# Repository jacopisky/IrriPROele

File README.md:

# IrriPROele
A simple irrigation controller system up to 6 AC and 4 DC valves + pump protection

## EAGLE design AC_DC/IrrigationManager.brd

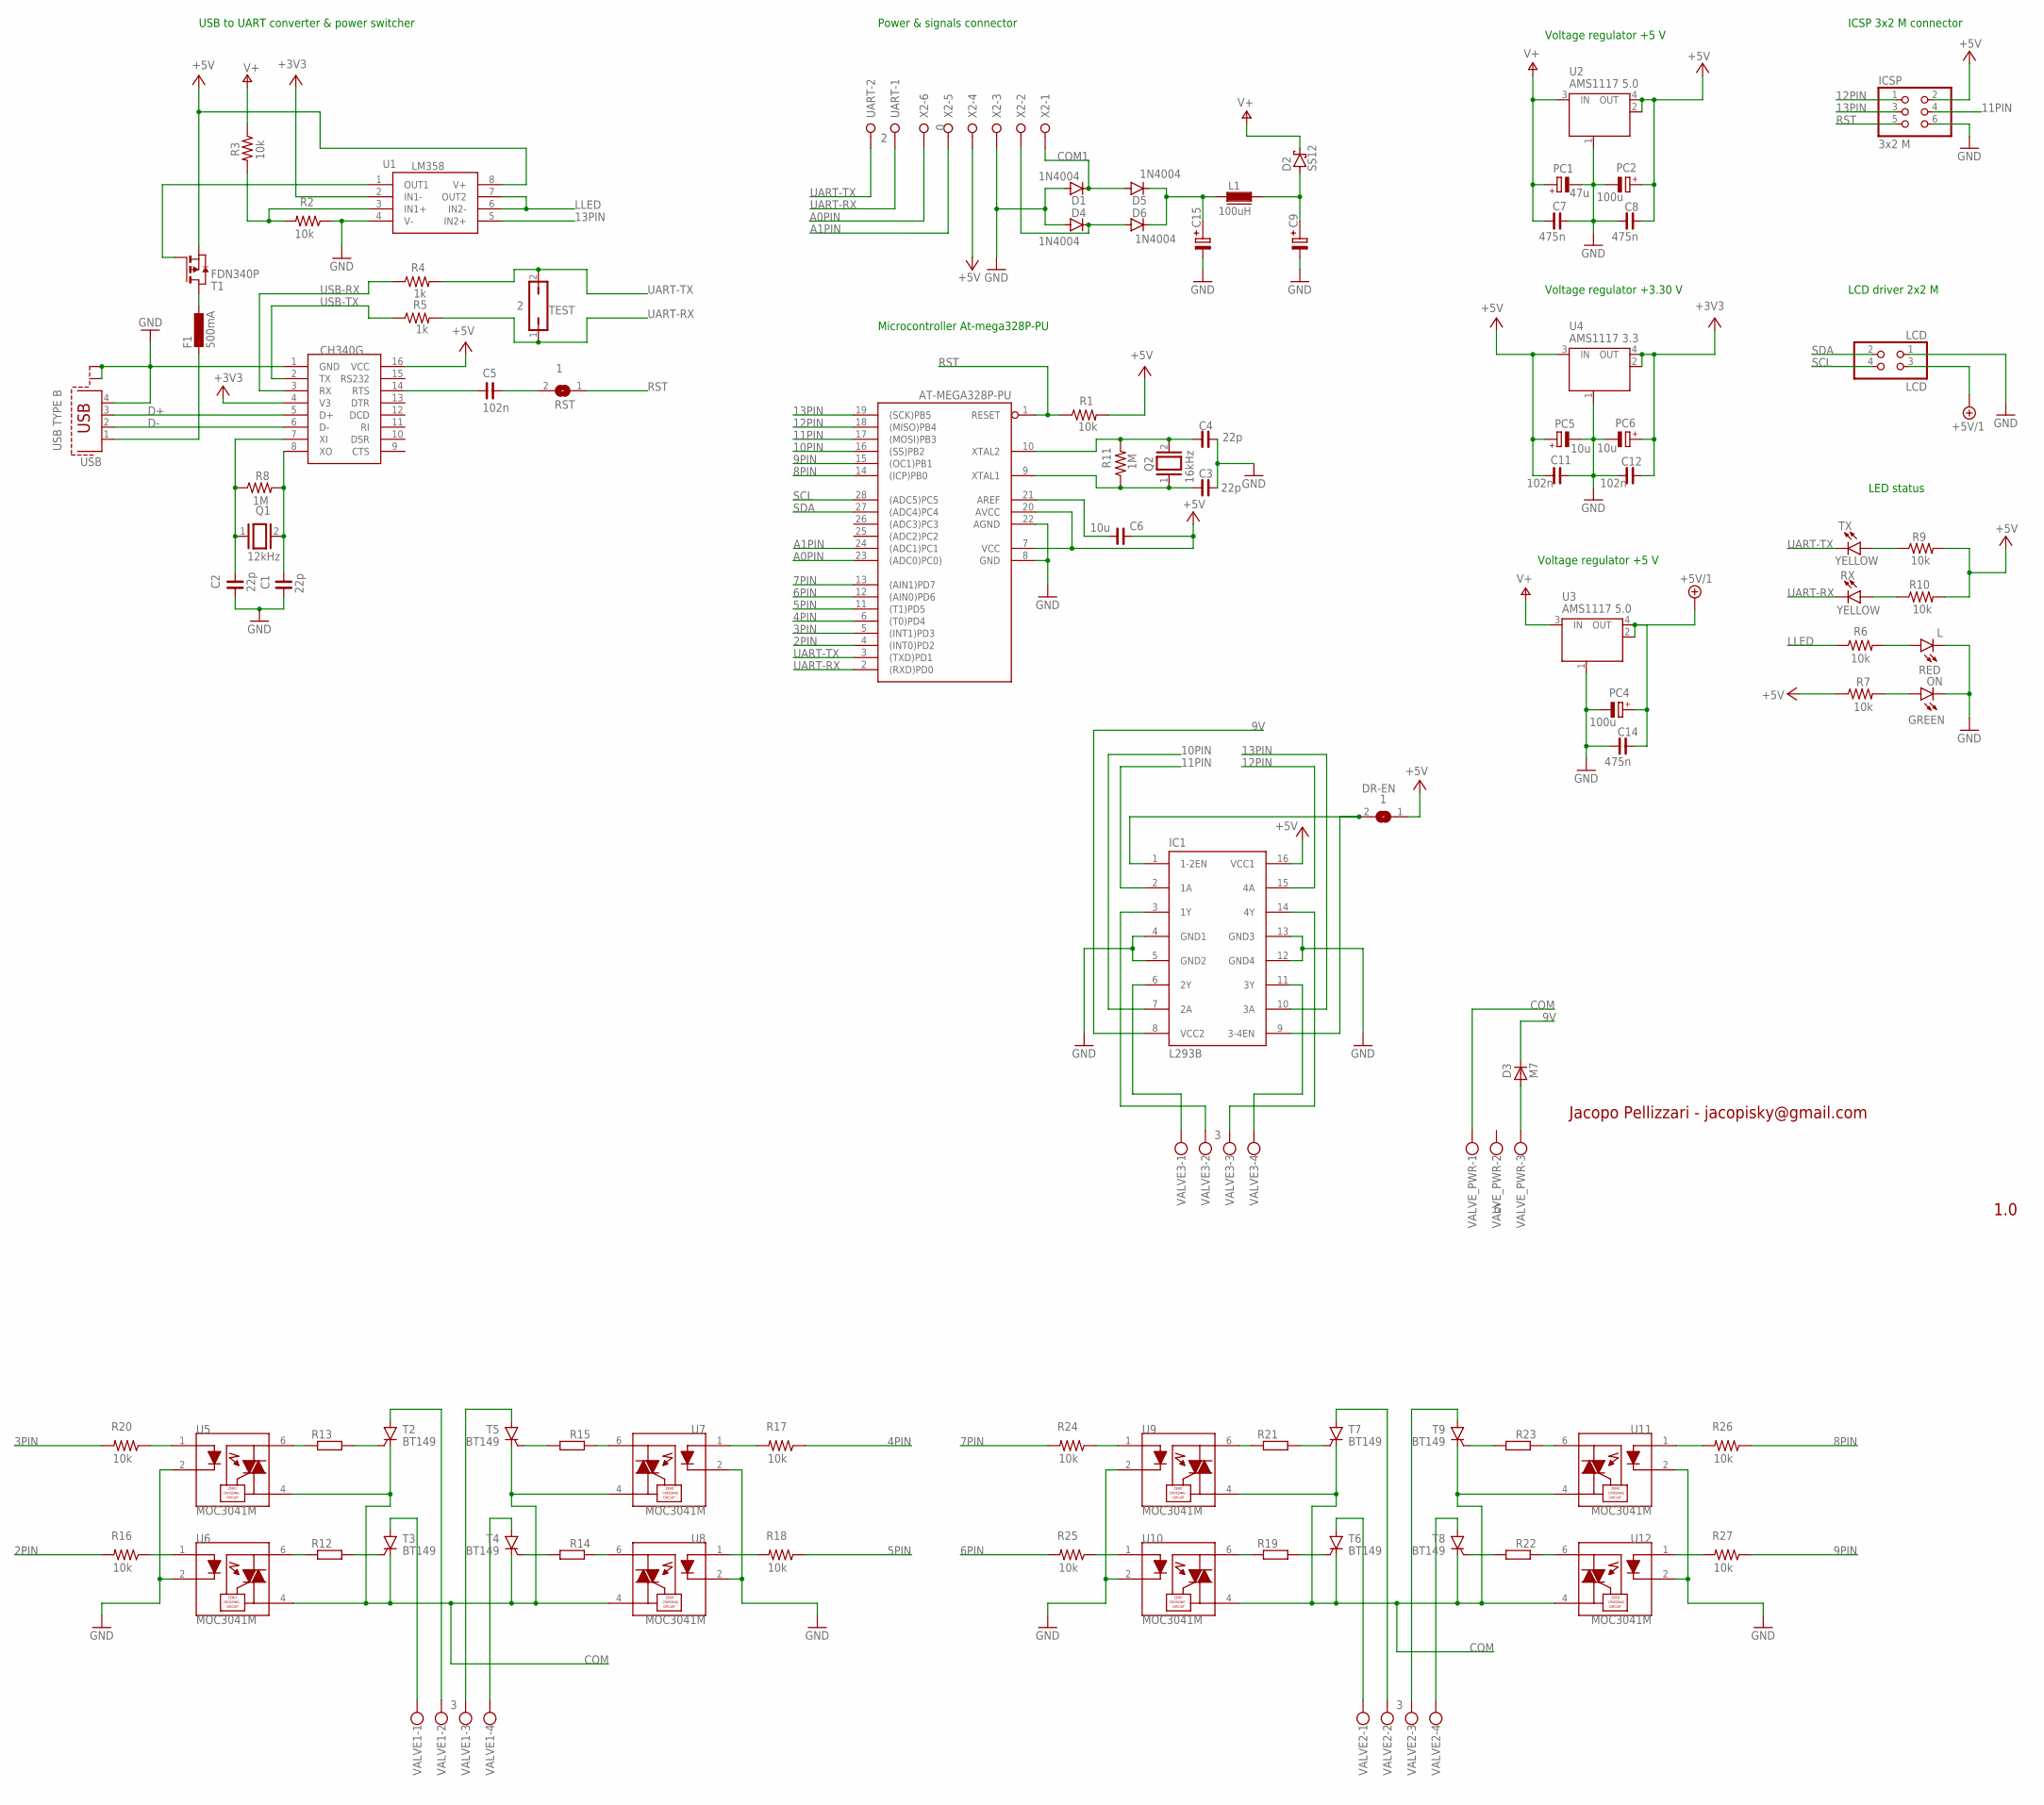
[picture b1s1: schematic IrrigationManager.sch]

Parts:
AT-MEGA328P-PU: ATMEGA328P-PU; DIL28-3
C1, C2, C3, C4: 22p; C1206
C5, C11, C12: 102n; C1206
C6: 10u; C1206
C7, C8, C14: 475n; C1206
C9, C15: C-PR-5,0X10; E5,0-10
D1, D4, D5, D6: 1N4004; DO41-10
D2: SS12; SMA
D3: M7; SMB
DR-EN: 1; SJ
F1: 500mA; L1812
IC1: L293B; DIL16
ICSP: 3x2 M; 2X03
L: RED; CHIPLED_1206
L1: 100uH; FASTRON_07HCP_INDUCTOR
LCD: LCD; 2X02
ON: GREEN; CHIPLED_1206
PC1: 47u; PANASONIC_D
PC2, PC4: 100u; PANASONIC_D
PC5, PC6: 10u; 153CLV-0405
Q1: 12kHz; QS
Q2: 16kHz; QS
R1, R2, R3, R6, R7, R9, R10, R16, R17, R18, R20, R24, R25, R26, R27: 10k; RES_1206
R4, R5: 1k; RES_1206
R8, R11: 1M; RES_1206
R12, R13, R14, R15, R19, R21, R22, R23: R-EU_0204/7; 0204/7
RST: 1; SJ
RX: YELLOW; CHIPLED_1206
T1: FDN340P; SOT-23
T2, T3, T4, T5, T6, T7, T8, T9: BT149; TO92-4
TEST: 2; JP1
TX: YELLOW; CHIPLED_1206
U1: LM358; LM358DR
U2, U3: AMS1117 5.0; SOT223
U4: AMS1117 3.3; SOT223
U5, U6, U7, U8, U9, U10, U11, U12: MOC3041M; DIP762W46P254L889H508Q6
U$1: CH340G; SOIC16
UART: 2; W237-132
USB: USB TYPE B; PN61729-S
VALVE1, VALVE2, VALVE3: 3; W237-4P
VALVE_PWR: 6; W237-133
X2: 0; W237-6P

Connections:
2PIN: AT-MEGA328P-PU.4 ((INT0)PD2), R16.2
3PIN: AT-MEGA328P-PU.5 ((INT1)PD3), R20.2
4PIN: AT-MEGA328P-PU.6 ((T0)PD4), R17.1
5PIN: AT-MEGA328P-PU.11 ((T1)PD5), R18.1
5VP: T1.3 (G), U1.1 (OUT1)
6PIN: AT-MEGA328P-PU.12 ((AIN0)PD6), R25.2
7PIN: AT-MEGA328P-PU.13 ((AIN1)PD7), R24.2
8PIN: AT-MEGA328P-PU.14 ((ICP)PB0), R26.1
9PIN: AT-MEGA328P-PU.15 ((OC1)PB1), R27.1
9V: D3.C, IC1.8 (VCC2)
10PIN: AT-MEGA328P-PU.16 ((SS)PB2), IC1.7 (2A)
11PIN: AT-MEGA328P-PU.17 ((MOSI)PB3), IC1.2 (1A), ICSP.4
12PIN: AT-MEGA328P-PU.18 ((MISO)PB4), IC1.15 (4A), ICSP.1
13PIN: AT-MEGA328P-PU.19 ((SCK)PB5), IC1.10 (3A), ICSP.3, U1.5 (IN2+)
+3V3: C12.2, PC6.+, U1.2 (IN1-), U4.2 (OUT), U4.4 (OUT), U$1.4 (V3)
+5V: AT-MEGA328P-PU.7 (VCC), AT-MEGA328P-PU.20 (AVCC), C6.2, C8.2, C11.1, DR-EN.1, IC1.16 (VCC1), ICSP.2, PC2.+, PC5.+, R1.2, R7.1, R9.2, R10.2, T1.2 (S), U1.8 (V+), U2.2 (OUT), U2.4 (OUT), U4.3 (IN), U$1.16 (VCC), X2.4
+5V/1: C14.2, LCD.3, PC4.+, U3.2 (OUT), U3.4 (OUT)
A0PIN: AT-MEGA328P-PU.23 ((ADC0)PC0)), X2.6
A1PIN: AT-MEGA328P-PU.24 ((ADC1)PC1), X2.5
COM: T2.C, T3.C, T4.C, T5.C, T6.C, T7.C, T8.C, T9.C, U5.4 (MT1), U6.4 (MT1), U7.4 (MT1), U8.4 (MT1), U9.4 (MT1), U10.4 (MT1), U11.4 (MT1), U12.4 (MT1), VALVE_PWR.1
COM1: D1.C, D5.A, X2.1
CRST: C5.1, U$1.14 (RTS)
D+: U$1.5 (D+), USB.3
D-: U$1.6 (D-), USB.2
FUSE5V: F1.1, T1.1 (D)
GND: AT-MEGA328P-PU.8 (GND), AT-MEGA328P-PU.22 (AGND), C1.1, C2.1, C3.2, C4.2, C7.2, C8.1, C9.-, C11.2, C12.1, C14.1, C15.-, D1.A, D4.A, IC1.4 (GND1), IC1.5 (GND2), IC1.12 (GND4), IC1.13 (GND3), ICSP.6, L.C, LCD.1, ON.C, PC1.-, PC2.-, PC4.-, PC5.-, PC6.-, R2.1, U1.4 (V-), U2.1 (GND/ADJ), U3.1 (GND/ADJ), U4.1 (GND/ADJ), U5.2 (C), U6.2 (C), U7.2 (C), U8.2 (C), U9.2 (C), U10.2 (C), U11.2 (C), U12.2 (C), U$1.1 (GND), USB.4, USB.S1, USB.S2, X2.3
HV10: IC1.6 (2Y), VALVE3.1
HV11: IC1.3 (1Y), VALVE3.2
HV12: IC1.14 (4Y), VALVE3.3
HV13: IC1.11 (3Y), VALVE3.4
LLED: R6.1, U1.6 (IN2-), U1.7 (OUT2)
unnamed: D3.A, VALVE_PWR.3
unnamed: C1.2, Q1.2, R8.2, U$1.8 (XO)
unnamed: C2.2, Q1.1, R8.1, U$1.7 (XI)
unnamed: AT-MEGA328P-PU.9 (XTAL1), C3.1, Q2.1, R11.1
unnamed: AT-MEGA328P-PU.10 (XTAL2), C4.1, Q2.2, R11.2
unnamed: R12.2, T3.G
unnamed: R12.1, U6.6 (MT2)
unnamed: R13.1, U5.6 (MT2)
unnamed: D4.C, D6.A, X2.2
unnamed: R2.2, R3.2, U1.3 (IN1+)
unnamed: C15.+, D5.C, D6.C, L1.1
unnamed: C5.2, RST.2
unnamed: T2.A, VALVE1.2
unnamed: DR-EN.2, IC1.1 (1-2EN), IC1.9 (3-4EN)
unnamed: C9.+, D2.A, L1.2
unnamed: T4.A, VALVE1.4
unnamed: R14.2, T4.G
unnamed: R14.1, U8.6 (MT2)
unnamed: R15.1, U7.6 (MT2)
unnamed: R13.2, T2.G
unnamed: R20.1, U5.1 (A)
unnamed: R15.2, T5.G
unnamed: R16.1, U6.1 (A)
unnamed: T5.A, VALVE1.3
unnamed: R9.1, TX.A
unnamed: R17.2, U7.1 (A)
unnamed: R18.2, U8.1 (A)
unnamed: T3.A, VALVE1.1
unnamed: T6.A, VALVE2.1
unnamed: R19.2, T6.G
unnamed: R19.1, U10.6 (MT2)
unnamed: R21.1, U9.6 (MT2)
unnamed: R21.2, T7.G
unnamed: T7.A, VALVE2.2
unnamed: T8.A, VALVE2.4
unnamed: R22.2, T8.G
unnamed: R22.1, U12.6 (MT2)
unnamed: R23.1, U11.6 (MT2)
unnamed: R23.2, T9.G
unnamed: T9.A, VALVE2.3
unnamed: R24.1, U9.1 (A)
unnamed: R25.1, U10.1 (A)
unnamed: R26.2, U11.1 (A)
unnamed: R10.1, RX.A
unnamed: R27.2, U12.1 (A)
unnamed: AT-MEGA328P-PU.21 (AREF), C6.1
P13LED: L.A, R6.2
PWRLED: ON.A, R7.2
RST: AT-MEGA328P-PU.1 (RESET), ICSP.5, R1.1, RST.1
SCL: AT-MEGA328P-PU.28 ((ADC5)PC5), LCD.4
SDA: AT-MEGA328P-PU.27 ((ADC4)PC4), LCD.2
UART-RX: AT-MEGA328P-PU.2 ((RXD)PD0), R5.2, RX.C, TEST.1, UART.1
UART-TX: AT-MEGA328P-PU.3 ((TXD)PD1), R4.2, TEST.2, TX.C, UART.2
USB5V: F1.2, USB.1
USB-RX: R4.1, U$1.3 (RX)
USB-TX: R5.1, U$1.2 (TX)
V+: C7.1, D2.C, PC1.+, R3.1, U2.3 (IN), U3.3 (IN)

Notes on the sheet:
Voltage regulator +5 V
Voltage regulator +3.30 V
ICSP 3x2 M connector
LCD driver 2x2 M
USB to UART converter & power switcher
Microcontroller At-mega328P-PU
Power & signals connector
1.0
Jacopo Pellizzari - jacopisky@gmail.com
LED status

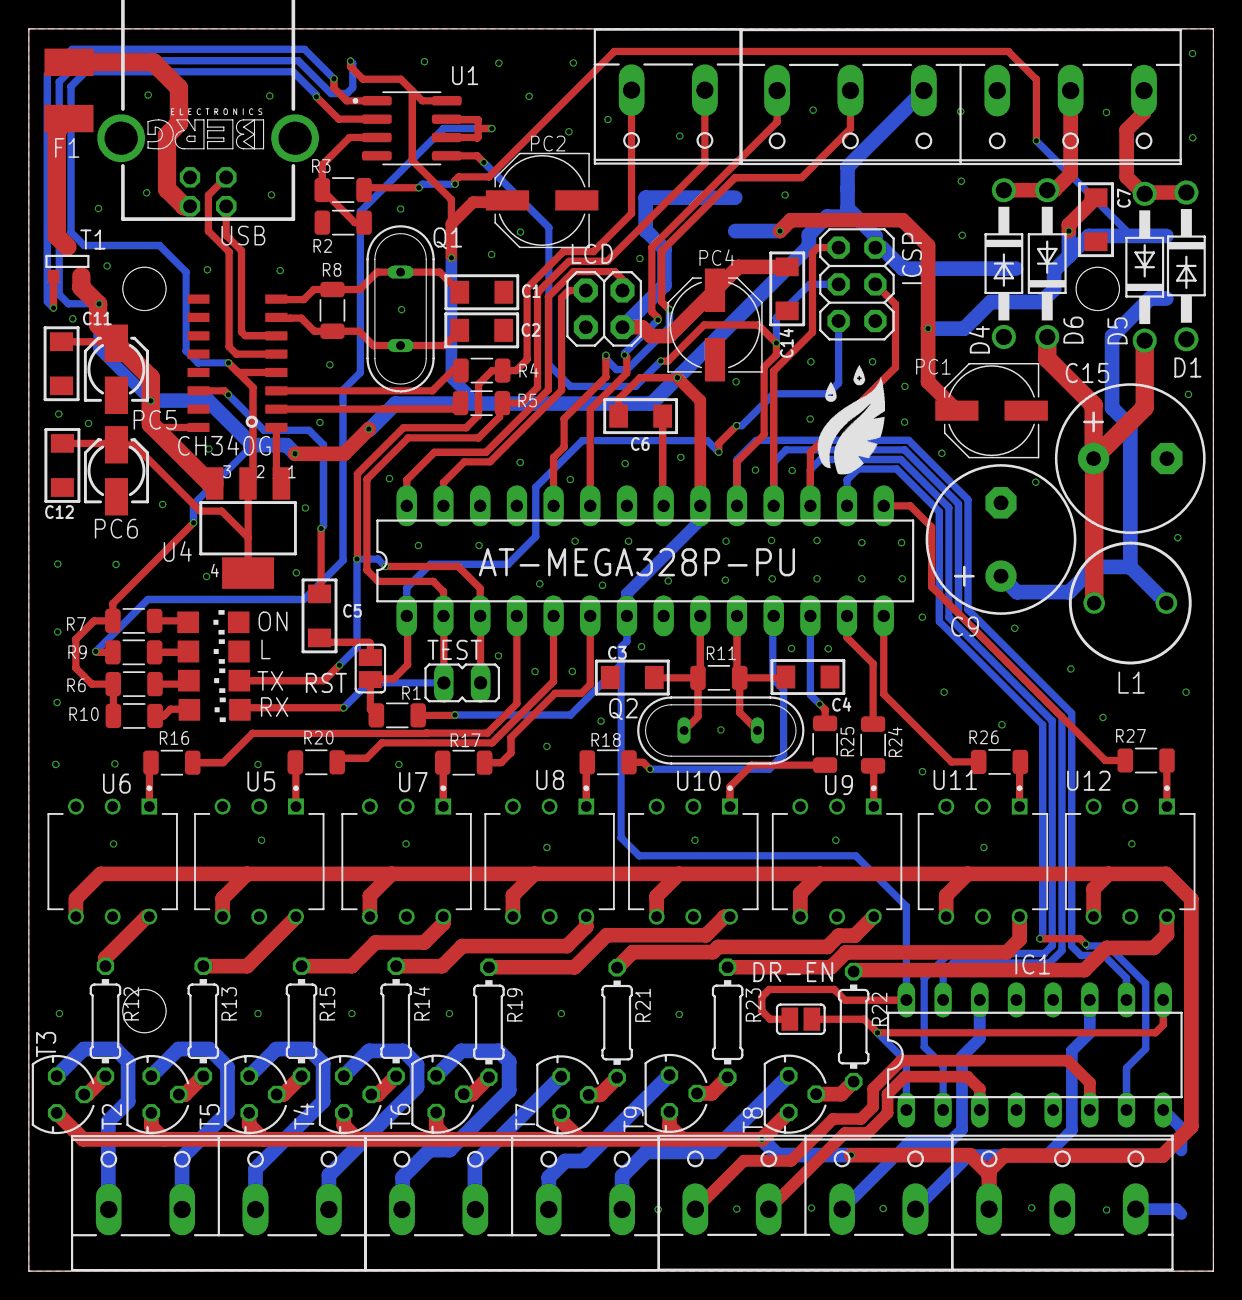
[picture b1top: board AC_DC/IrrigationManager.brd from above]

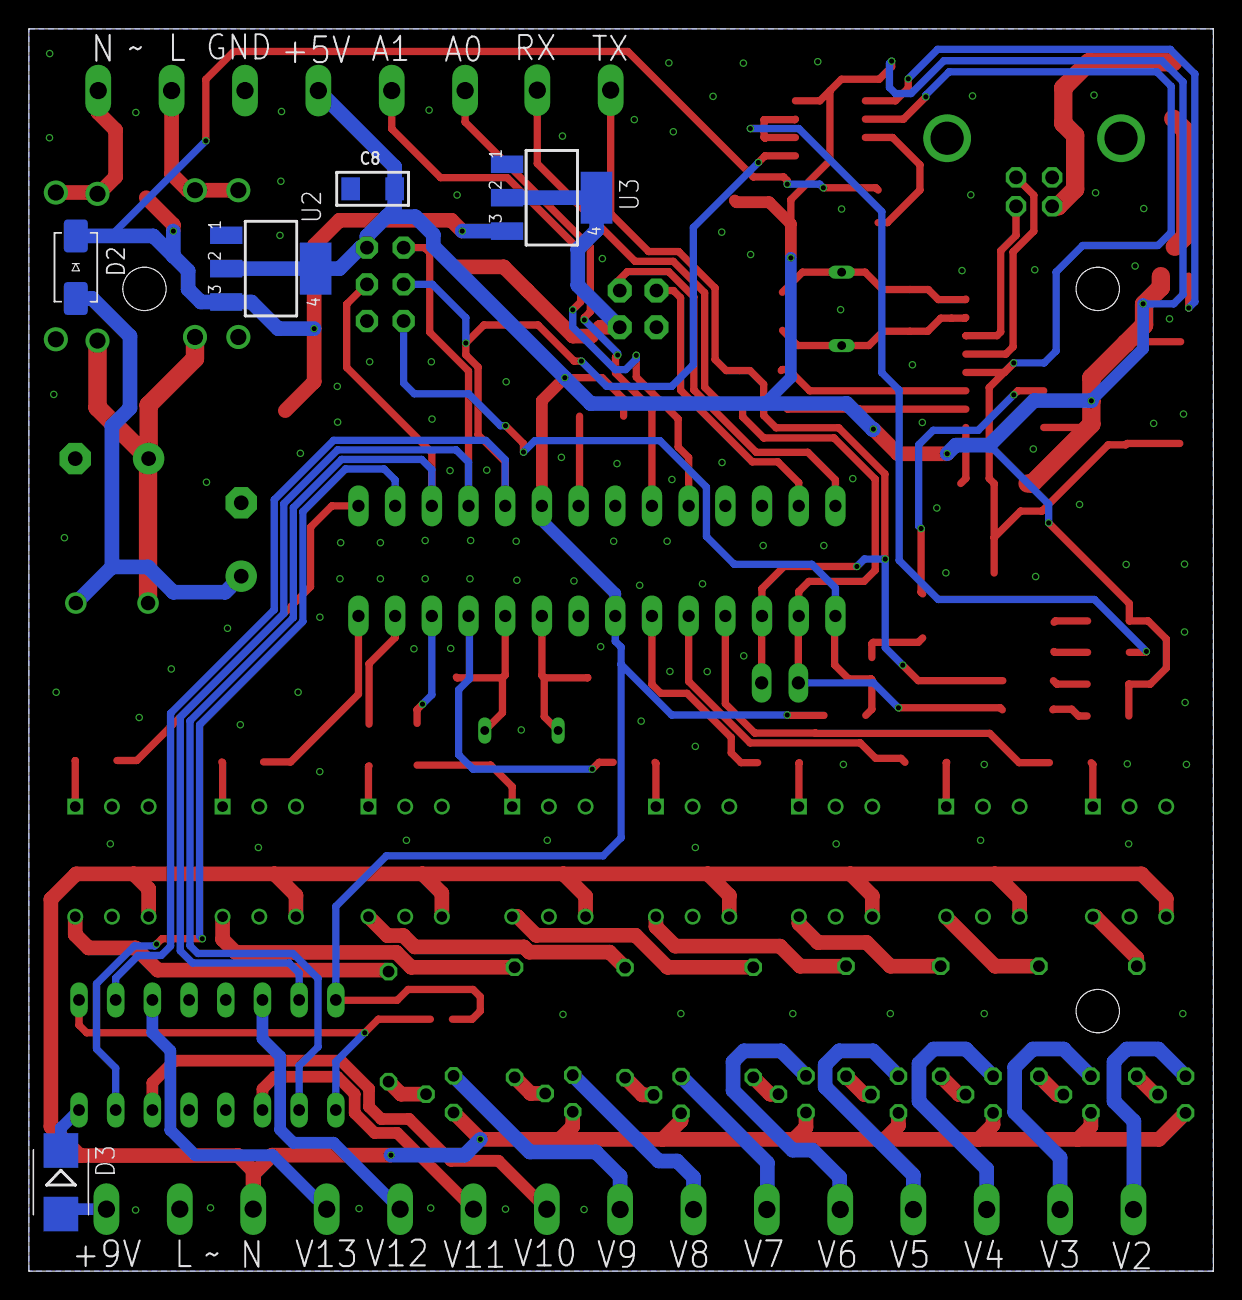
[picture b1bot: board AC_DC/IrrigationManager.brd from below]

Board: 2 copper layers, 82.0 x 86.0 mm, 95 parts (5 on the bottom side), 88 nets.

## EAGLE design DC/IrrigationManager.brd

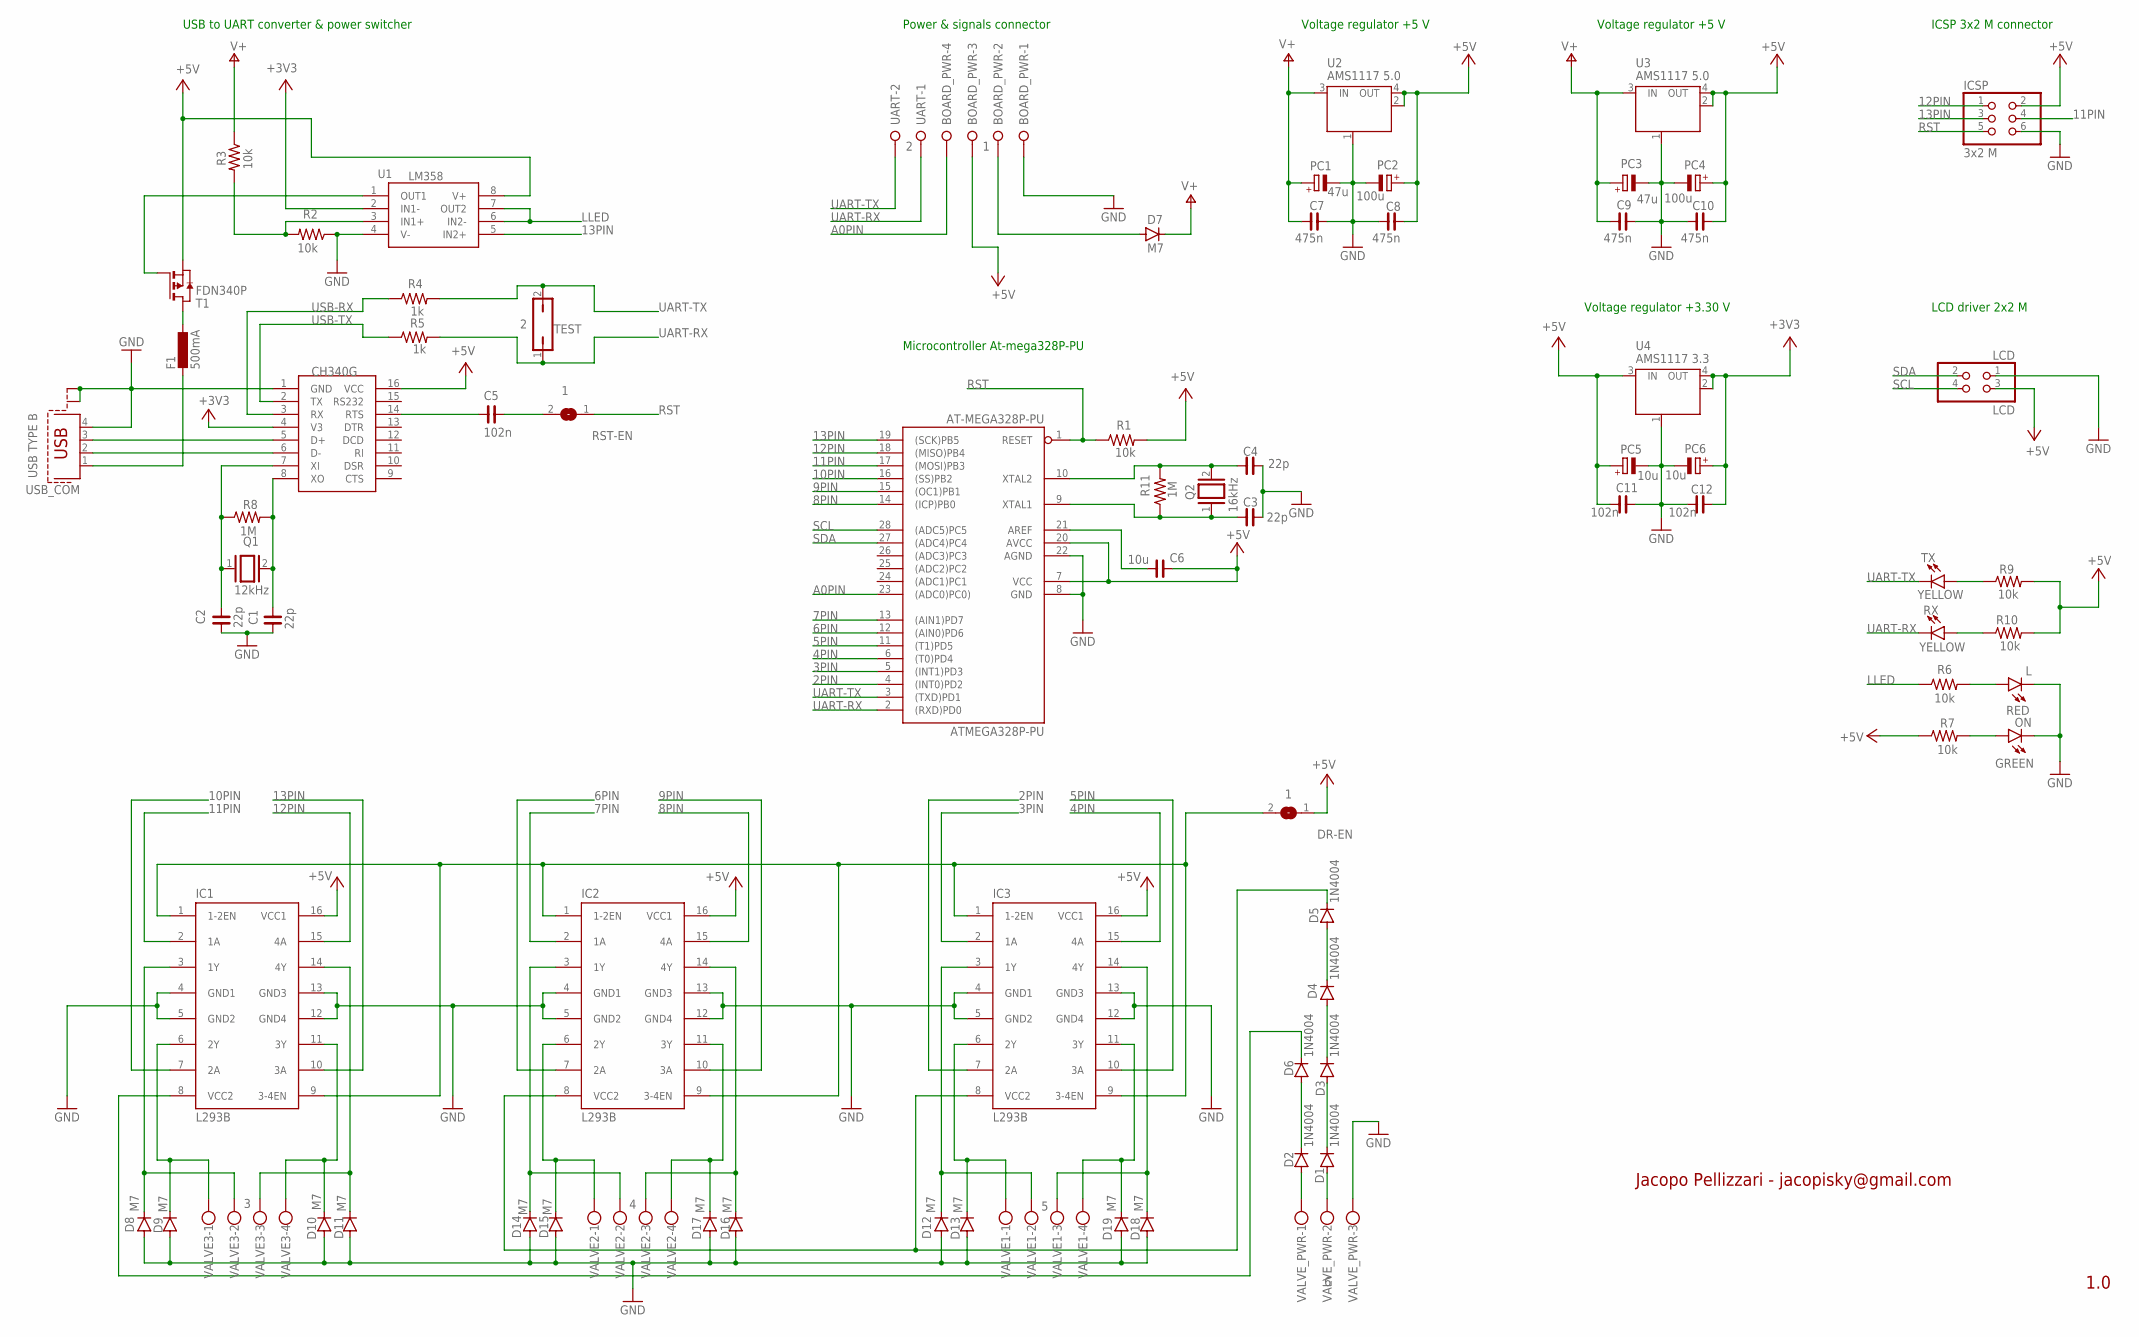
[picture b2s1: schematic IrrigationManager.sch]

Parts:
AT-MEGA328P-PU: ATMEGA328P-PU; DIL28-3
BOARD_PWR: 1; W237-4P
C1, C2, C3, C4: 22p; C1206
C5, C11, C12: 102n; C1206
C6: 10u; C1206
C7, C8, C9, C10: 475n; C1206
D1, D2, D3, D4, D5, D6: 1N4004; DO41-10
D7, D8, D9, D10, D11, D12, D13, D14, D15, D16, D17, D18, D19: M7; SMB
DR-EN: 1; SJ
F1: 500mA; L1812
IC1, IC2, IC3: L293B; DIL16
ICSP: 3x2 M; 2X03
L: RED; CHIPLED_1206
LCD: LCD; 2X02
ON: GREEN; CHIPLED_1206
PC1, PC3: 47u; PANASONIC_D
PC2, PC4: 100u; PANASONIC_D
PC5, PC6: 10u; 153CLV-0405
Q1: 12kHz; QS
Q2: 16kHz; QS
R1, R2, R3, R6, R7, R9, R10: 10k; RES_1206
R4, R5: 1k; RES_1206
R8, R11: 1M; RES_1206
RST-EN: 1; SJ
RX: YELLOW; CHIPLED_1206
T1: FDN340P; SOT-23
TEST: 2; JP1
TX: YELLOW; CHIPLED_1206
U1: LM358; LM358DR
U2, U3: AMS1117 5.0; SOT223
U4: AMS1117 3.3; SOT223
U$1: CH340G; SOIC16
UART: 2; W237-132
USB_COM: USB TYPE B; PN61729-S
VALVE1: 5; W237-4P
VALVE2: 4; W237-4P
VALVE3: 3; W237-4P
VALVE_PWR: 6; W237-133

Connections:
2PIN: AT-MEGA328P-PU.4 ((INT0)PD2), IC3.7 (2A)
3PIN: AT-MEGA328P-PU.5 ((INT1)PD3), IC3.2 (1A)
4PIN: AT-MEGA328P-PU.6 ((T0)PD4), IC3.15 (4A)
5PIN: AT-MEGA328P-PU.11 ((T1)PD5), IC3.10 (3A)
5VP: T1.3 (G), U1.1 (OUT1)
6PIN: AT-MEGA328P-PU.12 ((AIN0)PD6), IC2.7 (2A)
7PIN: AT-MEGA328P-PU.13 ((AIN1)PD7), IC2.2 (1A)
8PIN: AT-MEGA328P-PU.14 ((ICP)PB0), IC2.15 (4A)
9PIN: AT-MEGA328P-PU.15 ((OC1)PB1), IC2.10 (3A)
10PIN: AT-MEGA328P-PU.16 ((SS)PB2), IC1.7 (2A)
11PIN: AT-MEGA328P-PU.17 ((MOSI)PB3), IC1.2 (1A), ICSP.4
12PIN: AT-MEGA328P-PU.18 ((MISO)PB4), IC1.15 (4A), ICSP.1
13PIN: AT-MEGA328P-PU.19 ((SCK)PB5), IC1.10 (3A), ICSP.3, U1.5 (IN2+)
+3V3: C12.2, PC6.+, U1.2 (IN1-), U4.2 (OUT), U4.4 (OUT), U$1.4 (V3)
+5V: AT-MEGA328P-PU.7 (VCC), AT-MEGA328P-PU.20 (AVCC), BOARD_PWR.3, C6.2, C8.2, C10.2, C11.1, DR-EN.1, IC1.16 (VCC1), IC2.16 (VCC1), IC3.16 (VCC1), ICSP.2, LCD.3, PC2.+, PC4.+, PC5.+, R1.2, R7.1, R9.2, R10.2, T1.2 (S), U1.8 (V+), U2.2 (OUT), U2.4 (OUT), U3.2 (OUT), U3.4 (OUT), U4.3 (IN), U$1.16 (VCC)
+9V: D6.C, IC1.8 (VCC2)
+9V7: D2.C, D6.A
+10V4: D2.A, VALVE_PWR.1
+20V: D5.C, IC2.8 (VCC2), IC3.8 (VCC2)
+20V7: D4.C, D5.A
+21V4: D3.C, D4.A
+22V1: D1.C, D3.A
+22V8: D1.A, VALVE_PWR.2
A0PIN: AT-MEGA328P-PU.23 ((ADC0)PC0)), BOARD_PWR.4
CRST: C5.1, U$1.14 (RTS)
DRIVEREN: DR-EN.2, IC1.1 (1-2EN), IC1.9 (3-4EN), IC2.1 (1-2EN), IC2.9 (3-4EN), IC3.1 (1-2EN), IC3.9 (3-4EN)
FUSE5V: F1.1, T1.1 (D)
GND: AT-MEGA328P-PU.8 (GND), AT-MEGA328P-PU.22 (AGND), BOARD_PWR.1, C1.1, C2.1, C3.2, C4.2, C7.2, C8.1, C9.2, C10.1, C11.2, C12.1, D8.A, D9.A, D10.A, D11.A, D12.A, D13.A, D14.A, D15.A, D16.A, D17.A, D18.A, D19.A, IC1.4 (GND1), IC1.5 (GND2), IC1.12 (GND4), IC1.13 (GND3), IC2.4 (GND1), IC2.5 (GND2), IC2.12 (GND4), IC2.13 (GND3), IC3.4 (GND1), IC3.5 (GND2), IC3.12 (GND4), IC3.13 (GND3), ICSP.6, L.C, LCD.1, ON.C, PC1.-, PC2.-, PC3.-, PC4.-, PC5.-, PC6.-, R2.1, U1.4 (V-), U2.1 (GND/ADJ), U3.1 (GND/ADJ), U4.1 (GND/ADJ), U$1.1 (GND), USB_COM.4, USB_COM.S1, USB_COM.S2, VALVE_PWR.3
HV2: D13.C, IC3.6 (2Y), VALVE1.1
HV3: D12.C, IC3.3 (1Y), VALVE1.2
HV4: D18.C, IC3.14 (4Y), VALVE1.3
HV5: D19.C, IC3.11 (3Y), VALVE1.4
HV6: D15.C, IC2.6 (2Y), VALVE2.1
HV7: D14.C, IC2.3 (1Y), VALVE2.2
HV8: D16.C, IC2.14 (4Y), VALVE2.3
HV9: D17.C, IC2.11 (3Y), VALVE2.4
HV10: D9.C, IC1.6 (2Y), VALVE3.1
HV11: D8.C, IC1.3 (1Y), VALVE3.2
HV12: D11.C, IC1.14 (4Y), VALVE3.3
HV13: D10.C, IC1.11 (3Y), VALVE3.4
LLED: R6.1, U1.6 (IN2-), U1.7 (OUT2)
unnamed: C1.2, Q1.2, R8.2, U$1.8 (XO)
unnamed: C2.2, Q1.1, R8.1, U$1.7 (XI)
unnamed: U$1.6 (D-), USB_COM.2
unnamed: AT-MEGA328P-PU.9 (XTAL1), C3.1, Q2.1, R11.1
unnamed: AT-MEGA328P-PU.10 (XTAL2), C4.1, Q2.2, R11.2
unnamed: U$1.5 (D+), USB_COM.3
unnamed: R2.2, R3.2, U1.3 (IN1+)
unnamed: C5.2, RST-EN.2
unnamed: R9.1, TX.A
unnamed: R10.1, RX.A
unnamed: AT-MEGA328P-PU.21 (AREF), C6.1
P13LED: L.A, R6.2
PWRLED: ON.A, R7.2
RST: AT-MEGA328P-PU.1 (RESET), ICSP.5, R1.1, RST-EN.1
SCL: AT-MEGA328P-PU.28 ((ADC5)PC5), LCD.4
SDA: AT-MEGA328P-PU.27 ((ADC4)PC4), LCD.2
UART-RX: AT-MEGA328P-PU.2 ((RXD)PD0), R5.2, RX.C, TEST.1, UART.1
UART-TX: AT-MEGA328P-PU.3 ((TXD)PD1), R4.2, TEST.2, TX.C, UART.2
USB5V: F1.2, USB_COM.1
USB-RX: R4.1, U$1.3 (RX)
USB-TX: R5.1, U$1.2 (TX)
V+: C7.1, C9.1, D7.C, PC1.+, PC3.+, R3.1, U2.3 (IN), U3.3 (IN)
VIN: BOARD_PWR.2, D7.A

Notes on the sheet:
Voltage regulator +5 V
Voltage regulator +3.30 V
ICSP 3x2 M connector
LCD driver 2x2 M
USB to UART converter & power switcher
Microcontroller At-mega328P-PU
Power & signals connector
1.0
Jacopo Pellizzari - jacopisky@gmail.com

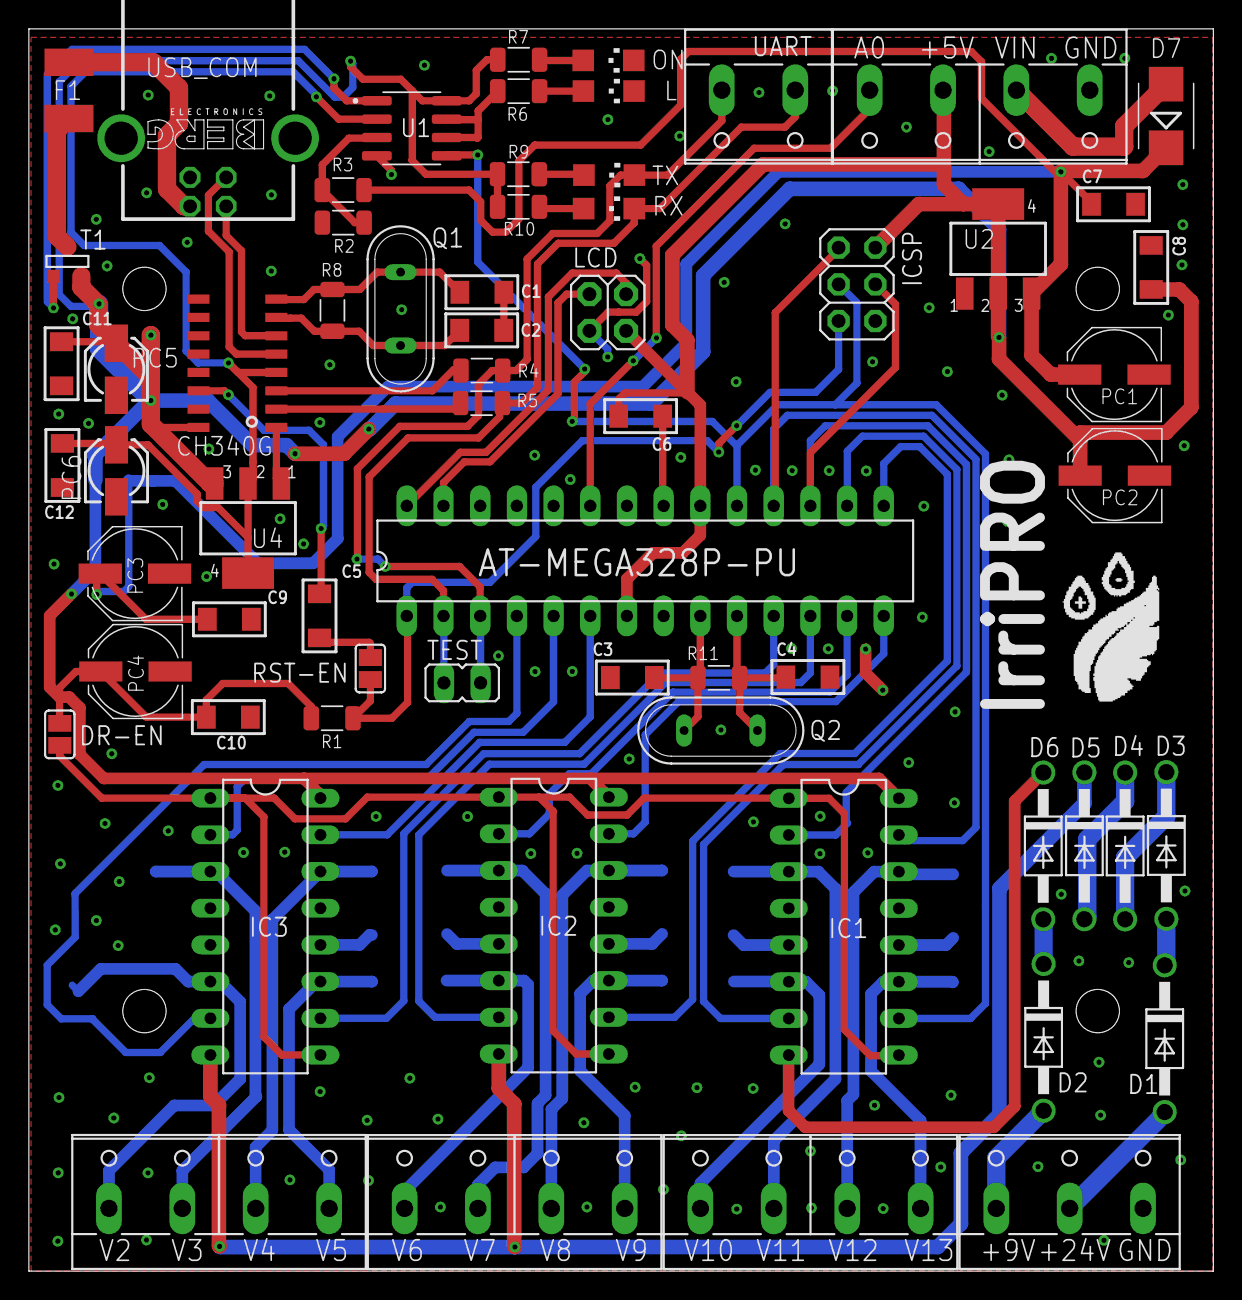
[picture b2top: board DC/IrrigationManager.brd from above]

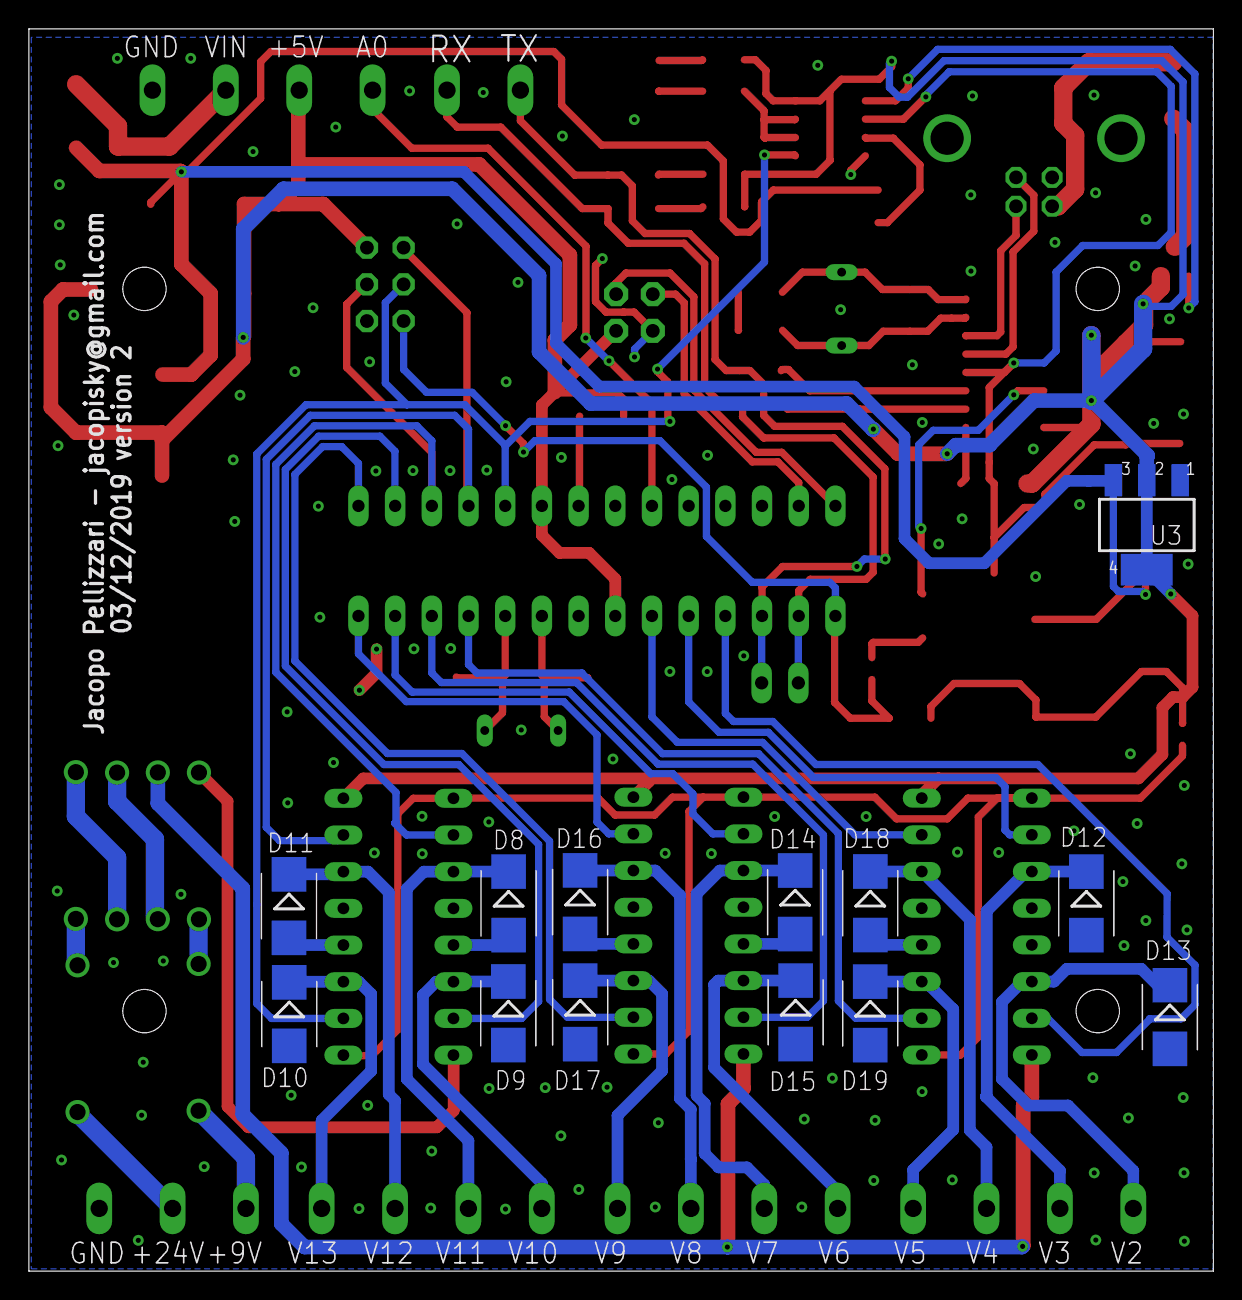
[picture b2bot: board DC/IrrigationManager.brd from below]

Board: 2 copper layers, 82.0 x 86.0 mm, 77 parts (13 on the bottom side), 64 nets.

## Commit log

2026-02-22 Adding both old full DC and new hybrid AC/DC controllers

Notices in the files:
parts and their libraries:
rc-master-smd: Copyright (C) 2007, Bob Starr
cap-pan40: Copyright (C) 2004, Bob Starr
